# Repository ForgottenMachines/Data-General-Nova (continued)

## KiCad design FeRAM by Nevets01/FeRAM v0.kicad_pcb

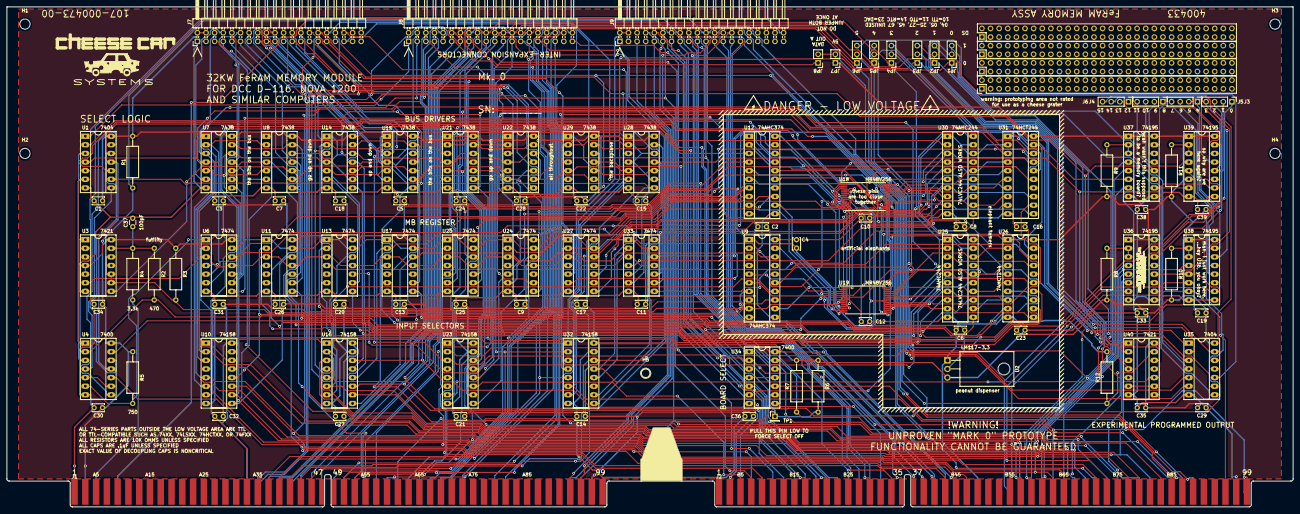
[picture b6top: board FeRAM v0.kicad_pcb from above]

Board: 2 copper layers, 379.0 x 147.3 mm, 117 parts (0 on the bottom side), 248 nets.

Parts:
C1, C2, C3, C4, C5, C6, C7, C8, C9, C10, C11, C12, C13, C14, C15, C16, C17, C18, C19, C20, C21, C22, C23, C24, C25, C26, C27, C28, C29, C30, C31, C32, C33, C34, C35, C36, C38, C39: .1uf; C_Disc_D3.4mm_W2.1mm_P2.50mm
C37: 100pf; C_Disc_D3.0mm_W1.6mm_P2.50mm
H1, H2, H3, H4, H5: MountingHole; MountingHole_3mm
J1: Slot_02x50_Odd_Even; portA_NovaMod
J2: Slot_02x50_Odd_Even; portB_NovaMod
J3, J4, J5, J6: Conn_01x04_Female; PinHeader_1x04_P2.54mm_Vertical
J7, J8, J9: Conn_02x20_Odd_Even; PinHeader_2x20_P2.54mm_Horizontal
JP1, JP2, JP3, JP4, JP5, JP6: Jumper_NC_Dual; PinHeader_1x03_P2.54mm_Vertical
JP7, JP8: Jumper; PinHeader_1x02_P2.54mm_Vertical
P0, P1, P2, P3: PinHeader_2x30_P2.54mm_Vertical
R1, R3, R6, R8, R9, R10, R11, R12: 10k; R_Axial_DIN0309_L9.0mm_D3.2mm_P15.24mm_Horizontal
R2, R7: 470; R_Axial_DIN0309_L9.0mm_D3.2mm_P15.24mm_Horizontal
R4: 3.3k; R_Axial_DIN0309_L9.0mm_D3.2mm_P15.24mm_Horizontal
R5: 750; R_Axial_DIN0309_L9.0mm_D3.2mm_P15.24mm_Horizontal
TP1: TestPoint; PinHeader_1x01_P2.54mm_Vertical
U1: 74HCT04; DIP-14_W7.62mm_Socket_LongPads
U2: LM1117-3.3; TO-220-3_Horizontal_TabDown
U3, U40: 74LS21; DIP-14_W7.62mm_Socket_LongPads
U4, U34: 74LS00; DIP-14_W7.62mm_Socket_LongPads
U6, U11, U13, U17, U20, U24, U27, U33: 74LS74; DIP-14_W7.62mm_Socket_LongPads
U7, U8, U14, U15, U21, U22, U28, U29: 74LS38; DIP-14_W7.62mm_Socket_LongPads
U9, U12: 74AHC374; DIP-20_W7.62mm_Socket_LongPads
U10, U16, U23, U32: 74LS158; DIP-16_W7.62mm_Socket_LongPads
U18, U19: MR48V256; TSOP-I-28_11.8x8mm_P0.55mm
U25, U26, U30, U31: 74HCT244; DIP-20_W7.62mm_Socket_LongPads
U35: 74LS04; DIP-14_W7.62mm_Socket_LongPads
U36, U37, U38, U39: 74LS195; DIP-16_W7.62mm_Socket_LongPads

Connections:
+3V3: C2.1, C4.1, C6.1, C8.1, C10.1, C12.1, U2.2, U9.20, U12.20, U18.7, U19.7, U25.20, U30.20
+5V: C1.1, C3.1, C5.1, C7.1, C9.1, C11.1, C13.1, C14.1, C15.1, C16.1, C17.1, C18.1, C19.1, C20.1, C21.1, C22.1, C23.1, C24.1, C25.1, C26.1, C27.1, C28.1, C29.1, C30.1, C31.1, C32.1, C33.1, C34.1, C35.1, C36.1, C38.1, C39.1, J1.3, J1.4, J1.97, J1.98, J2.3, J2.4, J2.97, J2.98, J7.2, J7.4, JP7.1, R1.2, R3.1, R5.1, R6.1, R7.2, R8.2, R9.2, R10.2, R11.2, U1.14, U2.3, U3.14, U4.14, U6.14, U7.14, U8.14, U10.16, U11.14, U13.14, U14.14, U15.14, U16.16, U17.14, U20.14, U21.14, U22.14, U23.16, U24.14, U26.20, U27.14, U28.14, U29.14, U31.20, U32.16, U33.14, U34.14, U35.14, U36.1, U36.16, U37.1, U37.16, U38.1, U38.16, U39.1, U39.16, U40.14
-5V: J1.6, R4.2
/60Hz: J2.6, J8.39
/+15v: J1.10, J9.40
/CLR: J1.50, J8.32
/DATIA: J1.44, J8.8
/DATIB: J1.42, J8.10
/DATIC: J1.54, J8.12
/DATOA: J1.58, J8.14, JP8.1
/DATOB: J1.56, J8.16
/DATOC: J1.48, J8.18
/DCH0: J2.33, J9.19
/DCHI: J2.37, J9.23
/DS0: JP4.3, U35.2
/DS1: JP1.3, U35.4
/DS2: JP5.3, U35.6
/DS3: JP2.3, U35.8
/DS4: JP6.3, U35.10
/DS5: JP3.3, U35.12
/INHIBIT: J2.30, J9.12, U34.2
/INTA: J1.40, J8.6
/IOPLS: J1.74, J8.40
/IO_SELECT: U36.10, U37.10, U38.10, U39.10, U40.8
/LOCATION: R6.2, TP1.1, U34.9
/MA1: U9.5, U18.8, U19.8
/MA2: U9.6, U18.5, U19.5
/MA3: U9.9, U18.9, U19.9
/MA4: U9.12, U18.2, U19.2
/MA5: U9.15, U18.28, U19.28
/MA6: U9.16, U18.3, U19.3
/MA7: U9.19, U18.4, U19.4
/MA8: U12.2, U18.10, U19.10
/MA9: U12.5, U18.11, U19.11
/MA10: U12.6, U18.12, U19.12
/MA11: U12.9, U18.13, U19.13
/MA12: U12.12, U18.14, U19.14
/MA13: U12.15, U18.15, U19.15
/MA14: U12.16, U18.16, U19.16
/MA15: U12.19, U18.17, U19.17
/MB_LOAD: J2.74, J9.16, U3.2
/MD1: U6.12, U9.4, U10.7
/MD2: U9.7, U10.12, U11.2
/MD3: U9.8, U10.9, U11.12
/MD4: U9.13, U13.2, U16.4
/MD5: U9.14, U13.12, U16.7
/MD6: U9.17, U16.12, U17.2
/MD7: U9.18, U16.9, U17.12
/MD8: U12.3, U20.2, U23.4
/MD9: U12.4, U20.12, U23.7
/MD10: U12.7, U23.12, U24.2
/MD11: U12.8, U23.9, U24.12
/MD12: U12.13, U27.2, U32.4
/MD13: U12.14, U27.12, U32.7
/MD14: U12.17, U32.12, U33.2
/MD15: U12.18, U32.9, U33.12
/OVFLO: J2.39, J9.25
/READ_1_S: U1.13, U4.8
/SELECT: R2.2, U3.1, U4.2, U4.5, U4.9, U34.1, U34.4, U34.11
/STROBE: J2.20, J9.10, U34.5
/STRT: J1.52, J8.34
/~CORE0: U19.26, U25.18, U26.2
/~CORE1: U19.25, U25.16, U26.4
/~CORE2: U19.24, U25.14, U26.6
/~CORE3: U19.23, U25.12, U26.8
/~CORE4: U19.22, U25.3, U26.17
/~CORE5: U19.20, U25.5, U26.15
/~CORE6: U19.19, U25.7, U26.13
/~CORE7: U19.18, U25.9, U26.11
/~CORE8: U18.26, U30.18, U31.2
/~CORE9: U18.25, U30.16, U31.4
/~CORE10: U18.24, U30.14, U31.6
/~CORE11: U18.23, U30.12, U31.8
/~CORE12: U18.22, U30.3, U31.17
/~CORE13: U18.20, U30.5, U31.15
/~CORE14: U18.19, U30.7, U31.13
/~CORE15: U18.18, U30.9, U31.11
/~DATA0: J2.62, J7.6, U7.3, U10.3, U36.4
/~DATA1: J2.65, J7.8, U7.6, U10.6, U36.5
/~DATA2: J2.82, J7.10, U7.8, U10.13, U36.6
/~DATA3: J2.73, J7.12, U7.11, U10.10, U36.7
/~DATA4: J2.61, J7.14, U14.3, U16.3, U38.4
/~DATA5: J2.57, J7.16, U14.6, U16.6, U38.5
/~DATA6: J2.95, J7.18, U14.8, U16.13, U38.6
/~DATA7: J2.55, J7.20, U14.11, U16.10, U38.7
/~DATA8: J2.60, J7.22, U21.3, U23.3, U37.4
/~DATA9: J2.63, J7.24, U21.6, U23.6, U37.5
/~DATA10: J2.75, J7.26, U21.8, U23.13, U37.6
/~DATA11: J2.58, J7.28, U21.11, U23.10, U37.7
/~DATA12: J2.59, J7.30, U28.3, U32.3, U39.4
/~DATA13: J2.64, J7.32, U28.6, U32.6, U39.5
/~DATA14: J2.56, J7.34, U28.8, U32.13, U39.6
/~DATA15: J2.66, J7.36, U28.11, U32.10, U39.7
/~DCHA: J1.60, J8.36
/~DCHP_IN: J1.94, J9.9
/~DCHP_OUT: J1.93, J9.5
/~DCHR: J2.35, J9.21
/~DCH_M0: J2.17, J9.13
/~DCH_M1: J2.21, J9.15
/~DRIVE_IO: J2.88, J9.22, U1.5
/~DS0: J1.72, J8.20, JP4.1, U35.1
/~DS1: J1.68, J8.22, JP1.1, U35.3
/~DS2: J1.66, J8.24, JP5.1, U35.5
/~DS3: J1.46, J8.26, JP2.1, U35.9
/~DS4: J1.62, J8.28, JP6.1, U35.11
/~DS5: J1.64, J8.30, JP3.1, U35.13
/~EXT_SELECT: J2.80, J9.18, R7.1, U34.13
/~INH0: U6.6, U25.2
/~INH1: U6.8, U25.4
/~INH2: U11.6, U25.6
/~INH3: U11.8, U25.8
/~INH4: U13.6, U25.17
/~INH5: U13.8, U25.15
/~INH6: U17.6, U25.13
/~INH7: U17.8, U25.11
/~INH8: U20.6, U30.2
/~INH9: U20.8, U30.4
/~INH10: U24.6, U30.6
/~INH11: U24.8, U30.8
/~INH12: U27.6, U30.17
/~INH13: U27.8, U30.15
/~INH14: U30.13, U33.6
/~INH15: U30.11, U33.8
/~INHIBIT_SELECT: J2.85, J9.28, U34.10
/~INHIBIT_S: U4.13, U18.6, U19.6, U25.1, U25.19, U30.1, U30.19, U34.3
/~INH_TRANS: J2.45, J9.29, R3.2, U3.9, U3.10, U3.12
/~INTP_IN: J1.96, J9.11
/~INTP_OUT: J1.95, J9.7
/~INTR: J2.29, J9.17
/~IORST: J1.70, J8.38
/~MA_LOAD: J2.7, J9.8, U1.1
/~MBO0: J2.79, J8.1, U10.2
/~MBO1: J2.77, J8.3, U10.5
/~MBO2: J2.44, J8.5, U10.14
/~MBO3: J2.43, J8.7, U10.11
/~MBO4: J2.42, J8.9, U16.2
/~MBO5: J2.32, J8.11, U16.5
/~MBO6: J2.16, J8.13, U16.14
/~MBO7: J2.14, J8.15, U16.11
/~MBO8: J2.12, J8.17, U23.2
/~MBO9: J2.9, J8.19, U23.5
/~MBO10: J2.8, J8.21, U23.14
/~MBO11: J2.5, J8.23, U23.11
/~MBO12: J1.39, J8.25, U32.2
/~MBO13: J1.37, J8.27, U32.5
/~MBO14: J1.43, J8.29, U32.14
/~MBO15: J1.41, J8.31, U32.11
/~MB_CLEAR: J2.86, J9.20, U1.9
/~MEM0: J2.71, J7.5, U8.3
/~MEM1: J2.70, J7.7, U8.6
/~MEM2: J2.47, J7.9, U8.8
/~MEM3: J2.68, J7.11, U8.11
/~MEM4: J2.28, J7.13, U15.3
/~MEM5: J2.26, J7.15, U15.6
/~MEM6: J2.22, J7.17, U15.8
/~MEM7: J2.24, J7.19, U15.11
/~MEM8: J1.55, J7.21, U22.3
/~MEM9: J1.53, J7.23, U22.6
/~MEM10: J1.45, J7.25, U22.8
/~MEM11: J1.51, J7.27, U22.11
/~MEM12: J1.36, J7.29, U29.3
/~MEM13: J1.35, J7.31, U29.6
/~MEM14: J2.76, J7.33, U29.8
/~MEM15: J2.18, J7.35, U29.11
/~MSK0: J1.38, J8.4
/~READ_1_S: U1.12, U4.12, U18.1, U19.1
/~READ_1: J2.87, J9.26, U4.10
/~READ_2: J2.90, J9.24
/~READ_IO: J2.83, J9.31, U10.1, U16.1, U23.1, U32.1
/~RELOAD_DISABLE: J2.72, J9.14, R1.1, U3.4, U3.5
/~RQENB: J2.41, J9.27
/~SELB: J1.82, J8.35
/~SELD: J1.80, J8.33
/~SNS0: U6.4, U26.18
/~SNS1: U6.10, U26.16
/~SNS2: U11.4, U26.14
/~SNS3: U11.10, U26.12
/~SNS4: U13.4, U26.3
/~SNS5: U13.10, U26.5
/~SNS6: U17.4, U26.7
/~SNS7: U17.10, U26.9
/~SNS8: U20.4, U31.18
/~SNS9: U20.10, U31.16
/~SNS10: U24.4, U31.14
/~SNS11: U24.10, U31.12
/~SNS12: U27.4, U31.3
/~SNS13: U27.10, U31.5
/~SNS14: U31.7, U33.4
/~SNS15: U31.9, U33.10
/~STROBE_S: U26.1, U26.19, U31.1, U31.19, U34.6
GND: C1.2, C2.2, C3.2, C4.2, C5.2, C6.2, C7.2, C8.2, C9.2, C10.2, C11.2, C12.2, C13.2, C14.2, C15.2, C16.2, C17.2, C18.2, C19.2, C20.2, C21.2, C22.2, C23.2, C24.2, C25.2, C26.2, C27.2, C28.2, C29.2, C30.2, C31.2, C32.2, C33.2, C34.2, C35.2, C36.2, C37.2, C38.2, C39.2, J1.1, J1.2, J1.33, J1.34, J1.99, J1.100, J2.1, J2.2, J2.50, J2.99, J2.100, J7.1, J7.3, J9.2, J9.4, R12.2, U1.7, U2.1, U3.7, U4.7, U6.7, U7.7, U8.7, U9.1, U9.10, U10.8, U10.15, U11.7, U12.1, U12.10, U13.7, U14.7, U15.7, U16.8, U16.15, U17.7, U18.21, U19.21, U20.7, U21.7, U22.7, U23.8, U23.15, U24.7, U25.10, U26.10, U27.7, U28.7, U29.7, U30.10, U31.10, U32.8, U32.15, U33.7, U34.7, U35.7, U36.8, U36.9, U37.8, U37.9, U38.8, U38.9, U39.8, U39.9, U40.7
unnamed: C37.1, R2.1, R4.1, U3.13
unnamed: J3.1, U36.15
unnamed: J3.2, U36.14
unnamed: J3.3, U36.13
unnamed: J3.4, U36.12
unnamed: J4.1, U37.15
unnamed: J4.2, U37.14
unnamed: J4.3, U37.13
unnamed: J4.4, U37.12
unnamed: J5.1, U38.15
unnamed: J5.2, U38.14
unnamed: J5.3, U38.13
unnamed: J5.4, U38.12
unnamed: J6.1, U39.15
unnamed: J6.2, U39.14
unnamed: J6.3, U39.13
unnamed: J6.4, U39.12
unnamed: JP1.2, U40.2
unnamed: JP2.2, U40.5
unnamed: JP3.2, U40.12
unnamed: JP4.2, U40.1
unnamed: JP5.2, U40.4
unnamed: JP6.2, U40.10
unnamed: JP7.2, JP8.2, R12.1, U40.13
unnamed: R5.2, U4.6, U6.1, U6.13, U11.1, U11.13, U13.1, U13.13, U17.1, U17.13, U20.1, U20.13, U24.1, U24.13, U27.1, U27.13, U33.1, U33.13
unnamed: R8.1, U36.2, U36.3
unnamed: R9.1, U37.2, U37.3
unnamed: R10.1, U38.2, U38.3
unnamed: R11.1, U39.2, U39.3
unnamed: U1.2, U9.11, U12.11
unnamed: U1.3, U4.3
unnamed: U1.4, U7.1, U7.4, U7.9, U7.12, U14.1, U14.4, U14.9, U14.12, U21.1, U21.4, U21.9, U21.12, U28.1, U28.4, U28.9, U28.12
unnamed: U1.6, U4.1
unnamed: U1.8, U4.4
unnamed: U1.10, U18.27, U19.27
unnamed: U1.11, U4.11
unnamed: U6.5, U7.2, U8.2
unnamed: U6.9, U7.5, U8.5
unnamed: U6.2, U10.4
unnamed: U7.10, U8.10, U11.5
unnamed: U7.13, U8.13, U11.9
unnamed: U3.6, U6.3, U6.11, U11.3, U11.11, U13.3, U13.11, U17.3, U17.11, U20.3, U20.11, U24.3, U24.11, U27.3, U27.11, U33.3, U33.11
unnamed: U13.5, U14.2, U15.2
unnamed: U13.9, U14.5, U15.5
unnamed: U14.10, U15.10, U17.5
unnamed: U14.13, U15.13, U17.9
unnamed: U3.8, U8.1, U8.4, U8.9, U8.12, U15.1, U15.4, U15.9, U15.12, U22.1, U22.4, U22.9, U22.12, U29.1, U29.4, U29.9, U29.12
unnamed: U20.5, U21.2, U22.2
unnamed: U20.9, U21.5, U22.5
unnamed: U21.10, U22.10, U24.5
unnamed: U21.13, U22.13, U24.9
unnamed: U27.5, U28.2, U29.2
unnamed: U27.9, U28.5, U29.5
unnamed: U28.10, U29.10, U33.5
unnamed: U28.13, U29.13, U33.9
unnamed: U34.8, U34.12
unnamed: U40.6, U40.9
